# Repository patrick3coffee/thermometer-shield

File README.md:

# The Idea
I wanted a display of temperature and humidity and it exploded into this shield that functions as a thermostat, humidistat, and optostat (if that's even a word).
This project is my first attempt at creating a pcb. The design work is done in KiCAD. 

## Docs
See the PDF for the full shcematic and the SVGs for the inverted copper etching masks.

## Logical units of functionality
1. Display: this 4 digit, 7-segment display is driven by shift registers and transistors.
2. ULN2804 breakout: a transistor array for controlling 8 resistive or inductive loads.
    * Channels A through D plus G and H terminate to screw terminals. Channels G and H are connected in parallel to A and B respectively. This increases current capacity
    * Channels E through H terminat to pin headers.
    * To use G and H independently, four traces must be cut on the bottom of the board and the exposed inputs must connect to a desired arduino pin.
3. Button Array: Four buttons alter the output voltage in an array of voltage dividers
4. Photoresistor: Measures light.
5. RHT03: Measure temperatre and humidity.
6. I2C pin headers: allow for greater hackability.
7. All unused pins exposed.
    * D9 and D12
    * A2 and A3.
    * A4 and A5 in I2C header, but can be used for any purpose.

## The progression of scope creep  
There was more to this list that I think I forgot about, but these are the high points.
* Display temperature and humidity in garage. (done on a breadboard)  
* Do the same in the chicken coop.
* Make the hum/temp readings control things at specified thresholds.
* Make those thresholds settable on the front panel.
* Add a light sensor because the chicken coop needs the door shut at sunset and opened at sunrise.
* Expose all unused pins in useful ways for hackability.

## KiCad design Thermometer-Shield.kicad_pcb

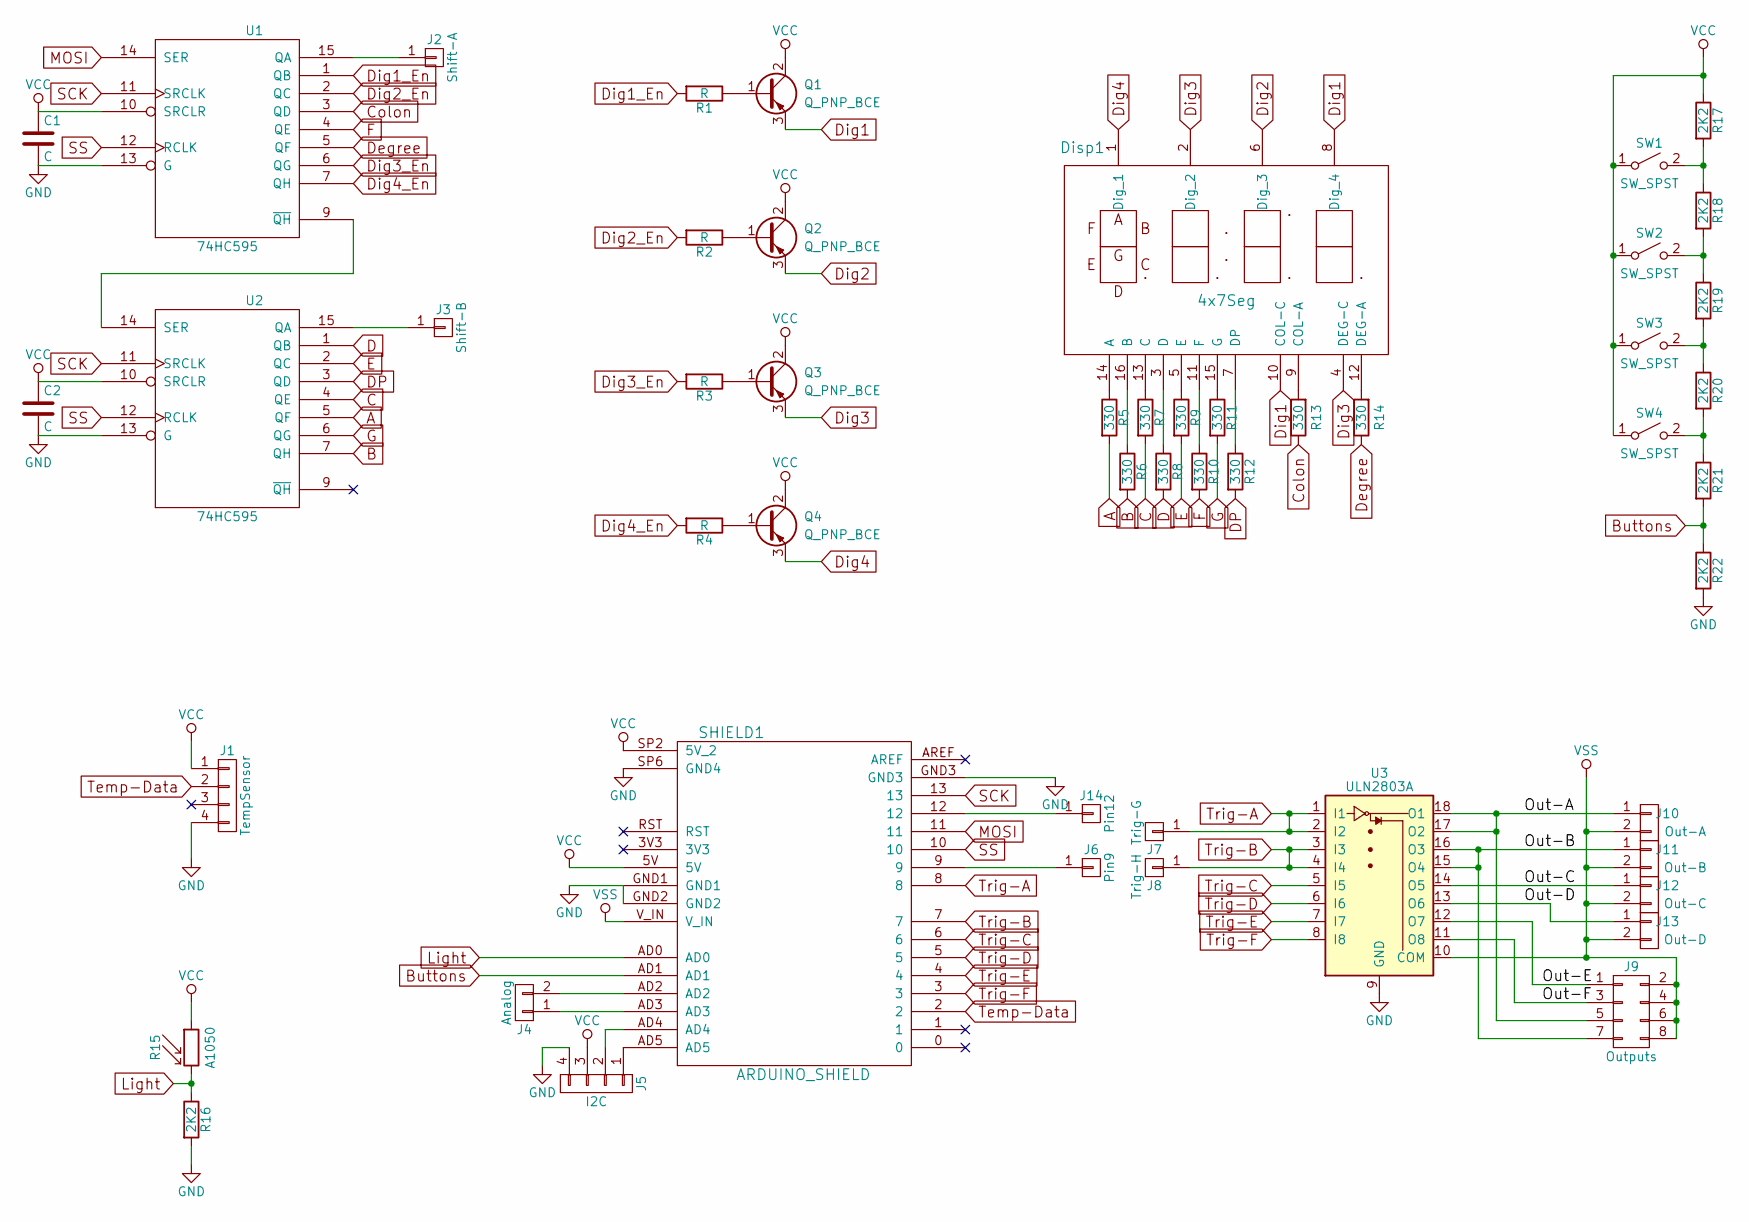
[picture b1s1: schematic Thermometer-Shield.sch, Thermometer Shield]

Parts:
C1, C2: C; C_Disc_D5.0mm_W2.5mm_P5.00mm
Disp1: 4x7Seg; ATA3492
J1: TempSensor; Pin_Header_Straight_1x04_Pitch2.54mm
J2: Shift-A; SolderWirePad_single_0-8mmDrill
J3: Shift-B; SolderWirePad_single_0-8mmDrill
J4: Analog; Pin_Header_Straight_1x02_Pitch2.54mm
J5: I2C; Pin_Header_Straight_1x04_Pitch2.54mm
J6: Pin9; Pin_Header_Straight_1x01_Pitch2.54mm
J7: Trig-G; SolderWirePad_single_0-8mmDrill
J8: Trig-H; SolderWirePad_single_0-8mmDrill
J9: Outputs; Pin_Header_Straight_2x04_Pitch2.54mm
J10: Out-A; AK300-2
J11: Out-B; AK300-2
J12: Out-C; AK300-2
J13: Out-D; AK300-2
J14: Pin12; Pin_Header_Straight_1x01_Pitch2.54mm
Q1, Q2, Q3, Q4: Q_PNP_BCE; TO-92_Inline_Narrow_Oval
R1, R2, R3, R4: R; R_0805_HandSoldering
R5, R6, R7, R8, R9, R10, R11, R12, R13, R14: 330; R_0603_HandSoldering
R15: A1050; Resistor_LDR_D6.4_RM3.4
R16, R17, R18, R19, R20, R21, R22: 2K2; R_0805_HandSoldering
SHIELD1: ARDUINO_SHIELD
SW1, SW2, SW3, SW4: SW_SPST; SW_PUSH_6mm
U1, U2: 74HC595; TSSOP-16_4.4x5mm_Pitch0.65mm
U3: ULN2803A; SOIC-18W_7.5x11.6mm_Pitch1.27mm

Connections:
/Out-A: J9.5, J10.1, U3.17 (O2), U3.18 (O1)
/Out-B: J9.7, J11.1, U3.15 (O4), U3.16 (O3)
/Out-C: J12.1, U3.14 (O5)
/Out-D: J13.1, U3.13 (O6)
/Out-E: J9.1, U3.12 (O7)
/Out-F: J9.3, U3.11 (O8)
A: R5.2, U2.5 (QF)
B: R6.2, U2.7 (QH)
Buttons: R21.2, R22.1, SHIELD1.AD1
C: R7.2, U2.4 (QE)
Colon: R13.1, U1.3 (QD)
D: R8.2, U2.1 (QB)
DP: R12.2, U2.3 (QD)
Degree: R14.1, U1.5 (QF)
Dig1: Disp1.8 (Dig_4), Disp1.10 (COL-C), Q1.3 (E)
Dig1_En: R1.2, U1.1 (QB)
Dig2: Disp1.6 (Dig_3), Q2.3 (E)
Dig2_En: R2.2, U1.2 (QC)
Dig3: Disp1.2 (Dig_2), Disp1.4 (DEG-C), Q3.3 (E)
Dig3_En: R3.2, U1.6 (QG)
Dig4: Disp1.1 (Dig_1), Q4.3 (E)
Dig4_En: R4.2, U1.7 (QH)
E: R9.2, U2.2 (QC)
F: R10.2, U1.4 (QE)
G: R11.2, U2.6 (QG)
GND: C1.2, C2.2, J1.4, J5.4, R16.2, R22.2, SHIELD1.GND1, SHIELD1.GND2, SHIELD1.GND3, SHIELD1.SP6 (GND4), U1.8 (GND), U1.13 (G), U2.8 (GND), U2.13 (G), U3.9 (GND)
Light: R15.2, R16.1, SHIELD1.AD0
MOSI: SHIELD1.11, U1.14 (SER)
unnamed: Disp1.3 (D), R8.1
unnamed: Disp1.5 (E), R9.1
unnamed: Disp1.7 (DP), R12.1
unnamed: Disp1.9 (COL-A), R13.2
unnamed: Disp1.11 (F), R10.1
unnamed: Disp1.12 (DEG-A), R14.2
unnamed: Disp1.13 (C), R7.1
unnamed: Disp1.14 (A), R5.1
unnamed: Disp1.15 (G), R11.1
unnamed: Disp1.16 (B), R6.1
unnamed: J2.1, U1.15 (QA)
unnamed: J3.1, U2.15 (QA)
unnamed: J4.1, SHIELD1.AD3
unnamed: J4.2, SHIELD1.AD2
unnamed: J5.1, SHIELD1.AD5
unnamed: J5.2, SHIELD1.AD4
unnamed: J6.1, SHIELD1.9
unnamed: J14.1, SHIELD1.12
unnamed: Q1.1 (B), R1.1
unnamed: Q2.1 (B), R2.1
unnamed: Q3.1 (B), R3.1
unnamed: Q4.1 (B), R4.1
unnamed: R17.2, R18.1, SW1.2 (B)
unnamed: R18.2, R19.1, SW2.2 (B)
unnamed: R19.2, R20.1, SW3.2 (B)
unnamed: R20.2, R21.1, SW4.2 (B)
unnamed: U1.9 (~QH), U2.14 (SER)
SCK: SHIELD1.13, U1.11 (SRCLK), U2.11 (SRCLK)
SS: SHIELD1.10, U1.12 (RCLK), U2.12 (RCLK)
Temp-Data: J1.2, SHIELD1.2
Trig-A: J7.1, SHIELD1.8, U3.1 (I1), U3.2 (I2)
Trig-B: J8.1, SHIELD1.7, U3.3 (I3), U3.4 (I4)
Trig-C: SHIELD1.6, U3.5 (I5)
Trig-D: SHIELD1.5, U3.6 (I6)
Trig-E: SHIELD1.4, U3.7 (I7)
Trig-F: SHIELD1.3, U3.8 (I8)
VCC: C1.1, C2.1, J1.1, J5.3, Q1.2 (C), Q2.2 (C), Q3.2 (C), Q4.2 (C), R15.1, R17.1, SHIELD1.5V, SHIELD1.SP2 (5V_2), SW1.1 (A), SW2.1 (A), SW3.1 (A), SW4.1 (A), U1.10 (SRCLR), U1.16 (VCC), U2.10 (SRCLR), U2.16 (VCC)
VSS: J9.2, J9.4, J9.6, J9.8, J10.2, J11.2, J12.2, J13.2, SHIELD1.V_IN, U3.10 (COM)

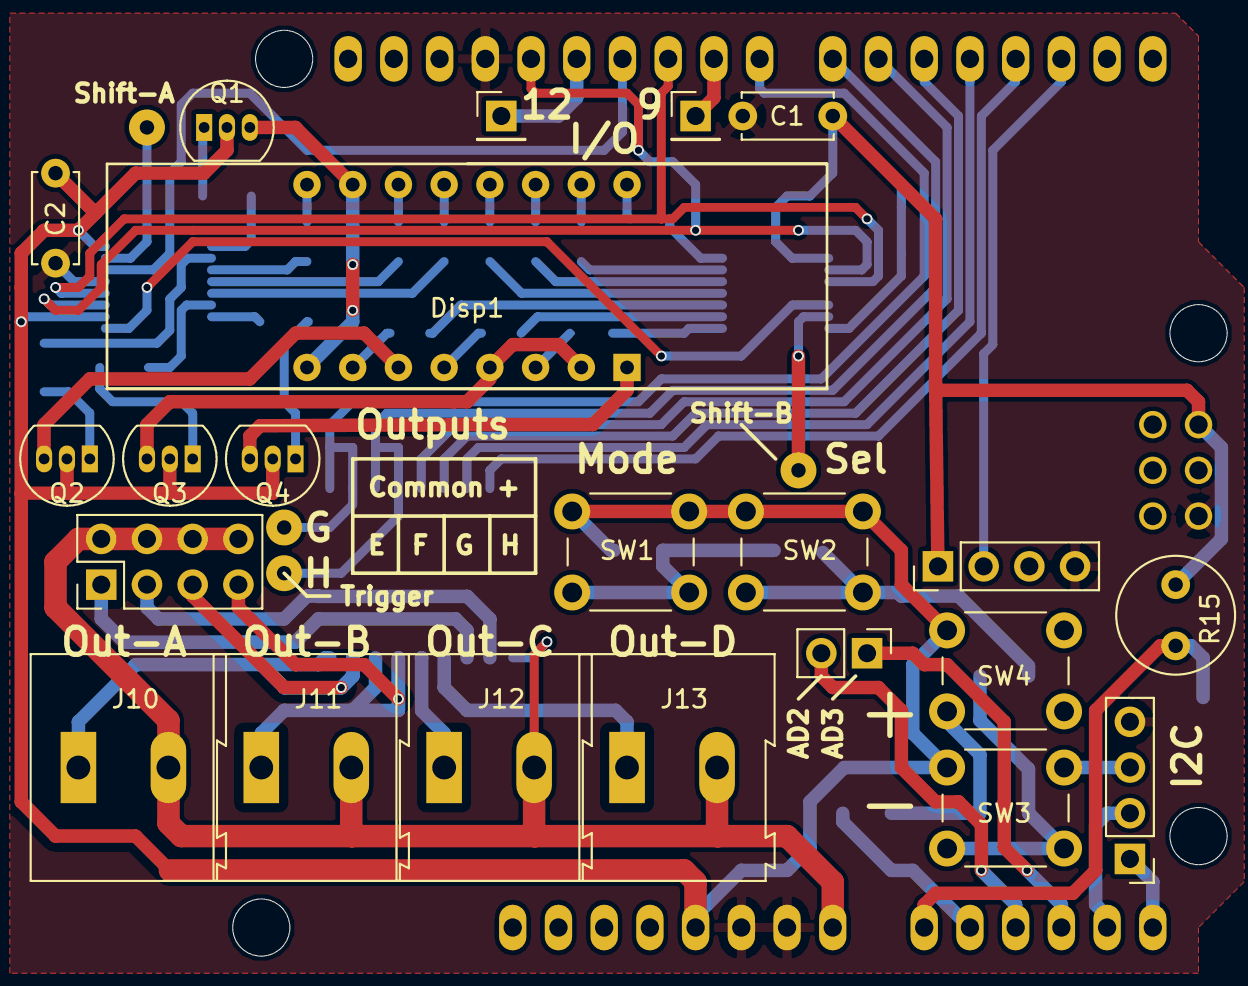
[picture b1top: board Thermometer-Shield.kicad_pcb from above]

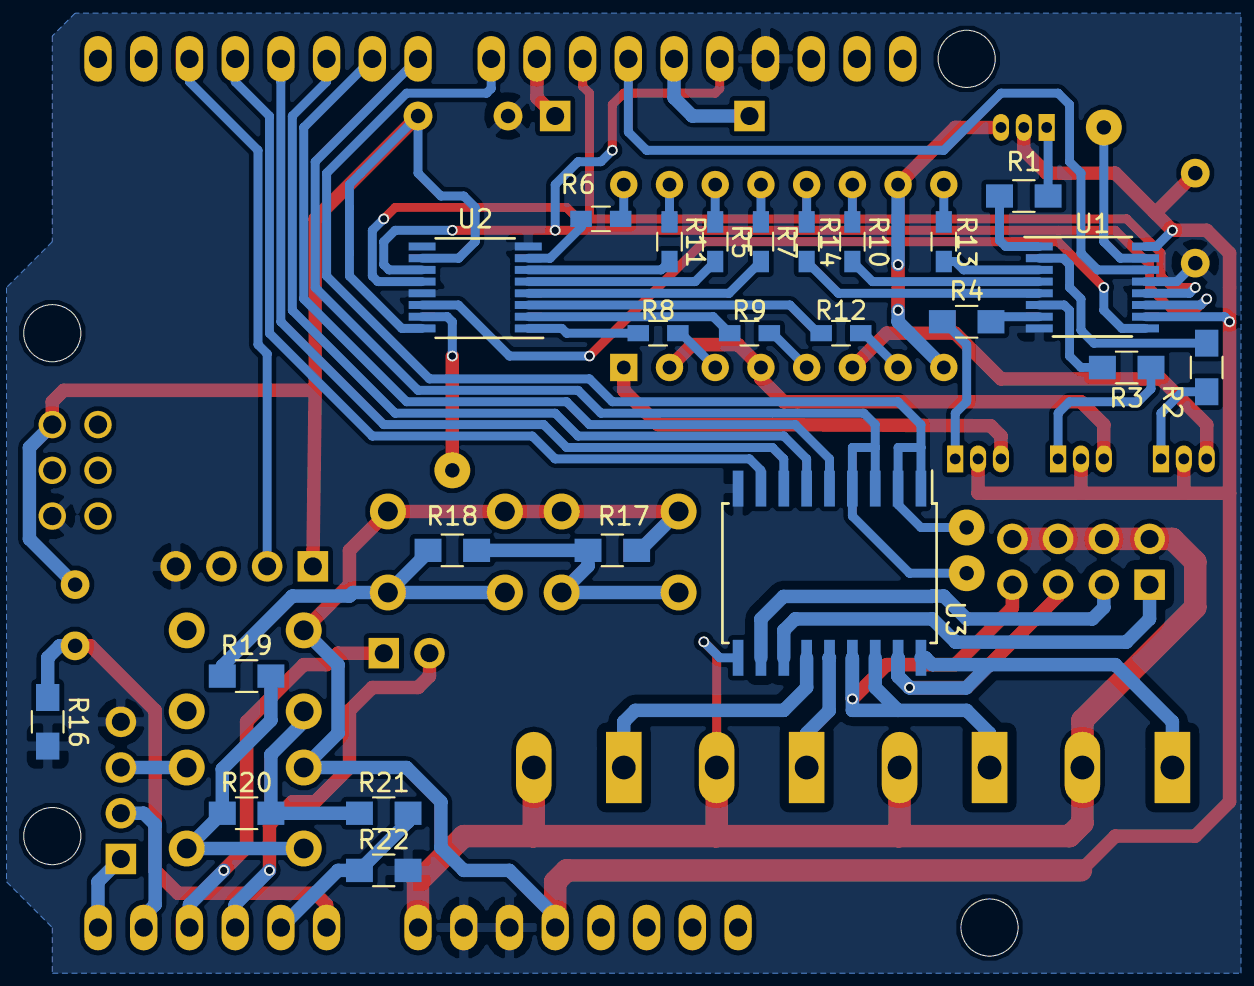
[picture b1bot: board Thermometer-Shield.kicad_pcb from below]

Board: 2 copper layers, 51 parts (24 on the bottom side), 66 nets.

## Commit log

2017-06-16 first commit. Schematic good, pcb needs love
2017-06-21 added documetation of parts, and some rework for more features
2017-06-21 added extension header with I2C layout
2017-06-25 started reworking for shift register
2017-06-26 schematic nearly done. PCB started
2017-07-05 completed schematic and pcb
2017-07-08 increased trace widths for etching
2017-07-08 minor trace tweaks
2017-07-08 added copper plots
2017-07-08 Added schematic
2017-07-10 changed schematic page size to us letter, and plotted
2017-07-13 arranged part labels for silk screen
2017-07-13 silk screen fixes and additions
